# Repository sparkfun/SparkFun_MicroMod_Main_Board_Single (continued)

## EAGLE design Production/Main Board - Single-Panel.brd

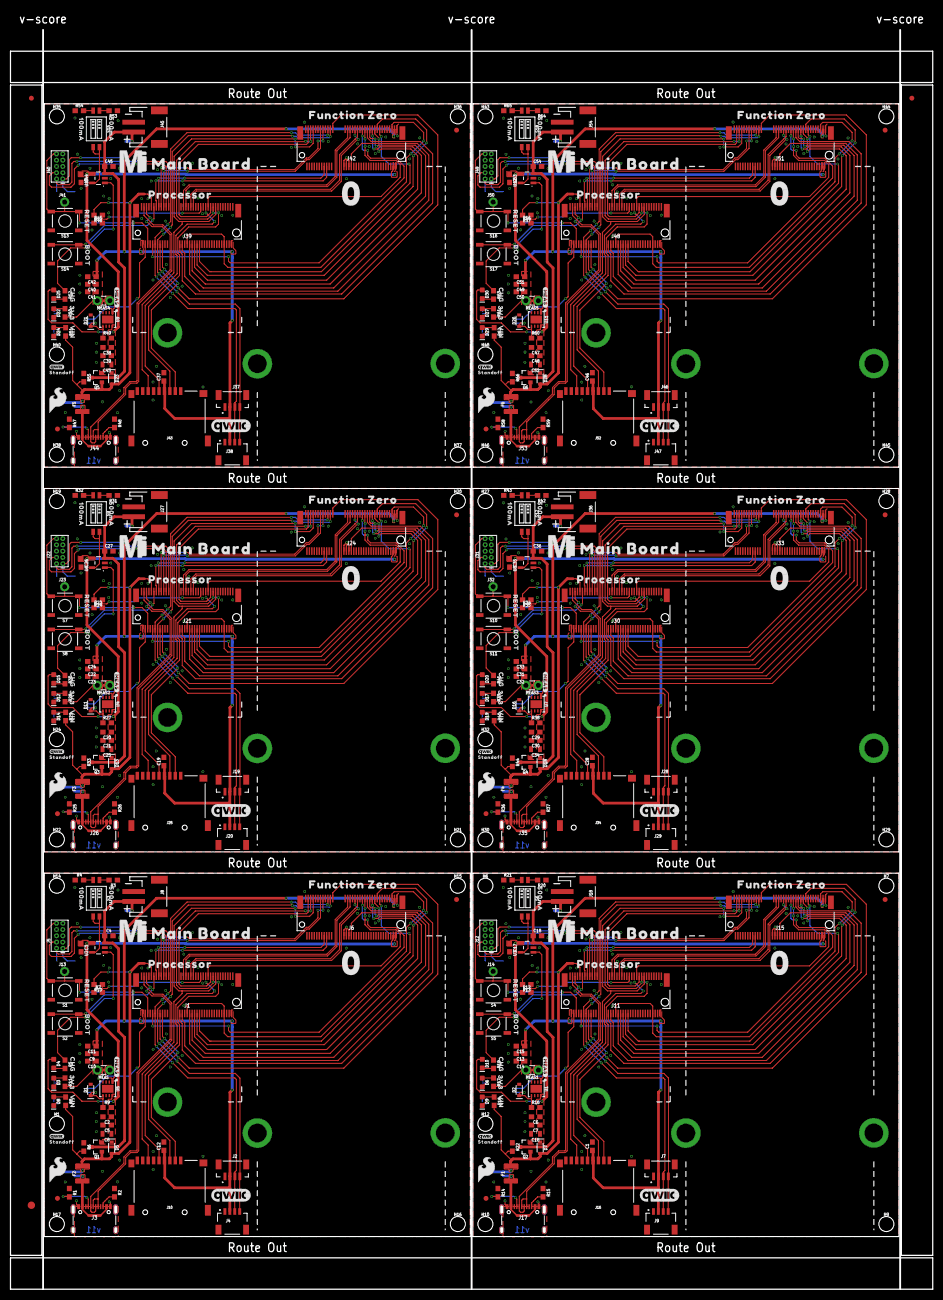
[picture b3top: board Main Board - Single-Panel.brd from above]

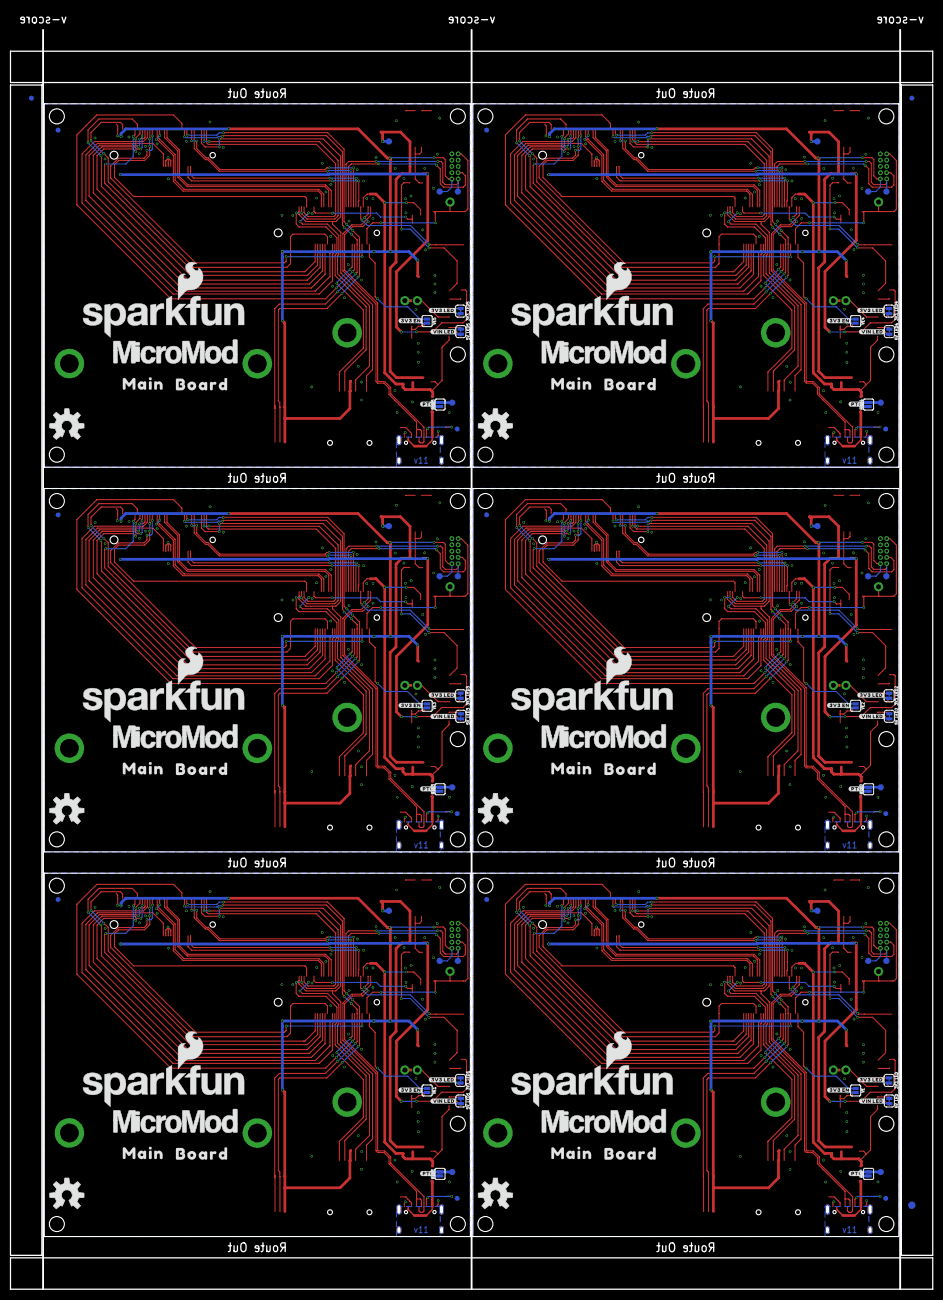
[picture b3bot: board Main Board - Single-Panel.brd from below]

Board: 2 copper layers, 186.9 x 255.3 mm, 534 parts (117 on the bottom side), 312 nets.

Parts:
3V3_LED, 3V3_LED1, 3V3_LED2, 3V3_LED3, 3V3_LED4, 3V3_LED5, 5V_LED, 5V_LED1, 5V_LED2, 5V_LED3, 5V_LED4, 5V_LED5: SMT-JUMPER_2_NC_TRACE_SILK
BYP, BYP1, BYP2, BYP3, BYP4, BYP5: JUMPER-SMT_2_NO_SILK; SMT-JUMPER_2_NO_SILK
C1, C5, C7, C10, C12, C14, C19, C21, C23, C28, C30, C32, C37, C39, C41, C46, C48, C50: 0.1uF; 0603
C2, C6, C11, C15, C20, C24, C29, C33, C38, C42, C47, C51: 0.22uF; 0603
C3, C4, C17, C18, C26, C27, C35, C36, C44, C45, C53, C54: 4.7uF; 0603
C8, C16, C25, C34, C43, C52: 10uF; 0805
C9, C13, C22, C31, C40, C49: 1.0uF; 0603
D1, D2, D11, D16, D21, D26: 3.3V; SOD-323
D3, D6, D8, D9, D12, D14, D17, D19, D22, D24, D27, D29: RED; LED-0603
D4, D10, D15, D20, D25, D30: Yellow; LED-0603
D5, D7, D13, D18, D23, D28: 3A/10V/280mV; SOD-323
E$1, E$2, E$3, E$4: FIDUCIAL-1X2
E$5, E$6: FIDUCIAL-1.5X3
F1, F2, F3, F4, F5, F6: 6V/2A; 1210
FD1, FD2, FD3, FD4, FD5, FD6, FD7, FD8, FD9, FD10, FD11, FD12, FD13, FD14, FD15, FD16, FD17, FD18, FD19, FD20, FD21, FD22, FD23, FD24: FIDUCIAL1X2; FIDUCIAL-1X2
H1, H6, H7, H9, H10, H12, H14, H15, H16, H17, H19, H20, H21, H22, H24, H27, H28, H29, H30, H32, H35, H36, H37, H38, H40, H43, H44, H45, H46, H48: STAND-OFFTIGHT; STAND-OFF-TIGHT
H2, H3, H4, H5, H8, H11, H13, H18, H23, H25, H26, H31, H33, H34, H39, H41, H42, H47: STAND-OFF-REFLOW-M2.5_2.5MM_TALL; STAND-OFF-REFLOW-M2.5
J1, J11, J21, J30, J39, J48: MICROMOD-2222-C; M.2-CONNECTOR-E
J2, J7, J19, J28, J37, J46: Vertical Qwiic Connector; JST04_1MM_VERT
J3, J17, J26, J35, J44, J53: USB-C-16P-2LAYER-PADS
J4, J9, J20, J29, J38, J47: QWIIC_RIGHT_ANGLE; JST04_1MM_RA
J5, J12, J22, J31, J40, J49: CORTEX_JTAG_DEBUG_MINIMUM_PTH; 2X5-PTH-1.27MM
J6, J15, J24, J33, J42, J51: MICROMOD_CARRIER; M.2-CONNECTOR-E-FUNCTION-STANDARD
J8, J18, J27, J36, J45, J54: JST-2-SMD
J10, J16, J25, J34, J43, J52: MICRO-SD-PUSH-PUSH-EXT-PIN; MICROSD-EXTERNALPIN
J13, J14, J23, J32, J41, J50: 1X01_NO_SILK
LOGO1, LOGO4, LOGO7, LOGO10, LOGO13, LOGO16: QWIIC_LOGO_8MM; QWIIC_8MM
LOGO2, LOGO5, LOGO8, LOGO11, LOGO14, LOGO17: SFE_LOGO_NAME_FLAME.3_INCH; SFE_LOGO_NAME_FLAME_.3
LOGO3, LOGO6, LOGO9, LOGO12, LOGO15, LOGO18: OSHW-LOGOL; OSHW-LOGO-L
MEAS, MEAS1, MEAS2, MEAS3, MEAS4, MEAS5: JUMPER-COMBO_2_NC_TRACE; COMBO-JUMPER_2_NC_TRACE
Q1, Q2, Q3, Q4, Q5, Q6: 3.1A/30V/105mΩ; SOT23-3
R1, R2, R14, R15, R25, R26, R36, R37, R47, R48, R58, R59: 5.1k; 0603
R3, R20, R31, R42, R53, R64: 2.0k; 0603
R4, R6, R7, R12, R21, R22, R23, R32, R33, R34, R43, R44, R45, R54, R55, R56, R65, R66: 10k; 0603
R5, R11, R17, R19, R28, R30, R39, R41, R50, R52, R61, R63: 1k; 0603
R8, R18, R29, R40, R51, R62: 4.7k; 0603
R9, R16, R27, R38, R49, R60: 100k; 0603
R10, R13, R24, R35, R46, R57: 20k; 0603
S1, S4, S7, S10, S13, S16: Reset; TACTILE_SWITCH_SMD_5.2MM
S2, S5, S8, S11, S14, S17: BOOT; TACTILE_SWITCH_SMD_5.2MM
S3, S6, S9, S12, S15, S18: DIP-02-SMD-50MIL; DIPSWITCH-02-50MIL
TP1, TP2, TP3, TP4, TP5, TP6, TP7, TP8, TP9, TP10, TP11, TP12, TP13, TP14, TP15, TP16, TP17, TP18, TP19, TP20, TP21, TP22, TP23, TP24: TEST-POINT3X5; PAD.03X.05
U1, U4, U5, U7, U9, U11: AP7361C-33; UDFN-8
U2, U3, U6, U8, U10, U12: MCP73831; SOT23-5
U$1, U$24, U$47, U$70, U$93, U$116: 3V332530
U$2, U$25, U$48, U$71, U$94, U$117: VIN32529
U$3, U$26, U$49, U$72, U$95, U$118: CHG32528
U$4, U$27, U$50, U$73, U$96, U$119: FUNCTION_ZERO517
U$5, U$28, U$51, U$74, U$97, U$120: PROCESSOR522
U$6, U$29, U$52, U$75, U$98, U$121: #3V3_LED#17
U$7, U$30, U$53, U$76, U$99, U$122: #VIN_LED#16
U$8, U$31, U$54, U$77, U$100, U$123: #PTC#18
U$9, U$32, U$55, U$78, U$101, U$124: BOOT32541
U$10, U$33, U$56, U$79, U$102, U$125: RESET32540
U$11, U$34, U$57, U$80, U$103, U$126: #3V3_EN#18
U$12, U$35, U$58, U$81, U$104, U$127: MICROMOD_MI_LOGO_1
U$13, U$36, U$59, U$82, U$105, U$128: 0525
U$14, U$42, U$65, U$88, U$111, U$134: MICROMOD_LOGO_1
U$15, U$37, U$60, U$83, U$106, U$129: MAIN523
U$16, U$38, U$61, U$84, U$107, U$130: BOARD524
U$17, U$39, U$62, U$85, U$108, U$131: 100MA6
U$18, U$40, U$63, U$86, U$109, U$132: 500MA101
U$19, U$41, U$64, U$87, U$110, U$133: MAIN_BOARD5523
U$20, U$43, U$66, U$89, U$112, U$135: QWIIC_3MM
U$21, U$44, U$67, U$90, U$113, U$136: STANDOFF501
U$22, U$45, U$68, U$91, U$114, U$137: SFE_LOGO_FLAME_.2
U$23, U$46, U$69, U$92, U$115, U$138: #MEAS#40313513
VE, VE1, VE2, VE3, VE4, VE5: SMT-JUMPER_2_NO_SILK

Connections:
3.3V: C9.1, C10.1, C11.1, C12.1, J1.2, J1.74, J2.2, J4.2, J5.1, J6.73, J10.4, MEAS.2, MEAS.4, R11.2, TP2.1
3.3V1: C1.1, C13.1, C14.1, C15.1, J7.2, J9.2, J11.2, J11.74, J12.1, J15.73, J16.4, MEAS1.2, MEAS1.4, R17.2, TP5.1
3.3V2: C19.1, C22.1, C23.1, C24.1, J19.2, J20.2, J21.2, J21.74, J22.1, J24.73, J25.4, MEAS2.2, MEAS2.4, R28.2, TP9.1
3.3V3: C28.1, C31.1, C32.1, C33.1, J28.2, J29.2, J30.2, J30.74, J31.1, J33.73, J34.4, MEAS3.2, MEAS3.4, R39.2, TP13.1
3.3V4: C37.1, C40.1, C41.1, C42.1, J37.2, J38.2, J39.2, J39.74, J40.1, J42.73, J43.4, MEAS4.2, MEAS4.4, R50.2, TP17.1
3.3V5: C46.1, C49.1, C50.1, C51.1, J46.2, J47.2, J48.2, J48.74, J49.1, J51.73, J52.4, MEAS5.2, MEAS5.4, R61.2, TP21.1
3.3V_EN: J1.4, VE.1
3.3V_EN1: J11.4, VE1.1
3.3V_EN2: J21.4, VE2.1
3.3V_EN3: J30.4, VE3.1
3.3V_EN4: J39.4, VE4.1
3.3V_EN5: J48.4, VE5.1
3.3V_EN_VE: D1.C, R9.1, U5.5, VE.2
3.3V_EN_VE1: D2.C, R16.1, U1.5, VE1.2
3.3V_EN_VE2: D11.C, R27.1, U4.5, VE2.2
3.3V_EN_VE3: D16.C, R38.1, U7.5, VE3.2
3.3V_EN_VE4: D21.C, R49.1, U9.5, VE4.2
3.3V_EN_VE5: D26.C, R60.1, U11.5, VE5.2
!BOOT!: J1.11, S2.3, S2.4
!BOOT!1: J11.11, S5.3, S5.4
!BOOT!2: J21.11, S8.3, S8.4
!BOOT!3: J30.11, S11.3, S11.4
!BOOT!4: J39.11, S14.3, S14.4
!BOOT!5: J48.11, S17.3, S17.4
!CS0!-PROCESSOR: J1.55, J6.49
!CS0!-PROCESSOR1: J11.55, J15.49
!CS0!-PROCESSOR2: J21.55, J24.49
!CS0!-PROCESSOR3: J30.55, J33.49
!CS0!-PROCESSOR4: J39.55, J42.49
!CS0!-PROCESSOR5: J48.55, J51.49
!RESET!: J1.6, J5.10, J13.1, S1.3, S1.4
!RESET!1: J11.6, J12.10, J14.1, S4.3, S4.4
!RESET!2: J21.6, J22.10, J23.1, S7.3, S7.4
!RESET!3: J30.6, J31.10, J32.1, S10.3, S10.4
!RESET!4: J39.6, J40.10, J41.1, S13.3, S13.4
!RESET!5: J48.6, J49.10, J50.1, S16.3, S16.4
A0-PROCESSOR: J1.34, J6.38
A0-PROCESSOR1: J11.34, J15.38
A0-PROCESSOR2: J21.34, J24.38
A0-PROCESSOR3: J30.34, J33.38
A0-PROCESSOR4: J39.34, J42.38
A0-PROCESSOR5: J48.34, J51.38
CTS1-PROCESSOR: J1.15, J6.16
CTS1-PROCESSOR1: J11.15, J15.16
CTS1-PROCESSOR2: J21.15, J24.16
CTS1-PROCESSOR3: J30.15, J33.16
CTS1-PROCESSOR4: J39.15, J42.16
CTS1-PROCESSOR5: J48.15, J51.16
D0-PROCESSOR: J1.10, J6.47
D0-PROCESSOR1: J11.10, J15.47
D0-PROCESSOR2: J21.10, J24.47
D0-PROCESSOR3: J30.10, J33.47
D0-PROCESSOR4: J39.10, J42.47
D0-PROCESSOR5: J48.10, J51.47
D1-PROCESSOR/SD_CARD_!CS!: J1.18, J10.2
D1-PROCESSOR/SD_CARD_!CS!1: J11.18, J16.2
D1-PROCESSOR/SD_CARD_!CS!2: J21.18, J25.2
D1-PROCESSOR/SD_CARD_!CS!3: J30.18, J34.2
D1-PROCESSOR/SD_CARD_!CS!4: J39.18, J43.2
D1-PROCESSOR/SD_CARD_!CS!5: J48.18, J52.2
D+: J1.3, J3.A6, J3.B6
D+1: J11.3, J17.A6, J17.B6
D+2: J21.3, J26.A6, J26.B6
D+3: J30.3, J35.A6, J35.B6
D+4: J39.3, J44.A6, J44.B6
D+5: J48.3, J53.A6, J53.B6
D-: J1.5, J3.A7, J3.B7
D-1: J11.5, J17.A7, J17.B7
D-2: J21.5, J26.A7, J26.B7
D-3: J30.5, J35.A7, J35.B7
D-4: J39.5, J44.A7, J44.B7
D-5: J48.5, J53.A7, J53.B7
G0-PROCESSOR: J1.40, J6.53
G0-PROCESSOR1: J11.40, J15.53
G0-PROCESSOR2: J21.40, J24.53
G0-PROCESSOR3: J30.40, J33.53
G0-PROCESSOR4: J39.40, J42.53
G0-PROCESSOR5: J48.40, J51.53
G1-PROCESSOR: J1.42, J6.55
G1-PROCESSOR1: J11.42, J15.55
G1-PROCESSOR2: J21.42, J24.55
G1-PROCESSOR3: J30.42, J33.55
G1-PROCESSOR4: J39.42, J42.55
G1-PROCESSOR5: J48.42, J51.55
G2-PROCESSOR: J1.44, J6.57
G2-PROCESSOR1: J11.44, J15.57
G2-PROCESSOR2: J21.44, J24.57
G2-PROCESSOR3: J30.44, J33.57
G2-PROCESSOR4: J39.44, J42.57
G2-PROCESSOR5: J48.44, J51.57
G3-PROCESSOR: J1.46, J6.59
G3-PROCESSOR1: J11.46, J15.59
G3-PROCESSOR2: J21.46, J24.59
G3-PROCESSOR3: J30.46, J33.59
G3-PROCESSOR4: J39.46, J42.59
G3-PROCESSOR5: J48.46, J51.59
G4-PROCESSOR: J1.48, J6.61
G4-PROCESSOR1: J11.48, J15.61
G4-PROCESSOR2: J21.48, J24.61
G4-PROCESSOR3: J30.48, J33.61
G4-PROCESSOR4: J39.48, J42.61
G4-PROCESSOR5: J48.48, J51.61
GND: 3V3_LED.1, 5V_LED.1, C2.2, C3.2, C4.2, C5.2, C8.2, C9.2, C10.2, C11.2, C12.2, D1.A, H3.1, H4.1, H8.1, J1.1, J1.7, J1.33, J1.36, J1.39, J1.45, J1.75, J2.1, J3.GND, J3.GND2, J4.1, J5.3, J5.5, J5.9, J6.1, J6.32, J6.33, J6.34, J6.36, J6.39, J6.45, J6.75, J8.1, J10.6, J10.10, J10.11, J10.12, J10.13, R1.1, R2.1, R3.1, R4.1, R6.1, R7.1, S1.1, S1.2, S2.1, S2.2, U2.2, U5.4, U5.EP
GND1: 3V3_LED1.1, 5V_LED1.1, C1.2, C6.2, C7.2, C13.2, C14.2, C15.2, C16.2, C17.2, C18.2, D2.A, H2.1, H5.1, H11.1, J7.1, J9.1, J11.1, J11.7, J11.33, J11.36, J11.39, J11.45, J11.75, J12.3, J12.5, J12.9, J15.1, J15.32, J15.33, J15.34, J15.36, J15.39, J15.45, J15.75, J16.6, J16.10, J16.11, J16.12, J16.13, J17.GND, J17.GND2, J18.1, R12.1, R14.1, R15.1, R20.1, R21.1, R22.1, S4.1, S4.2, S5.1, S5.2, U1.4, U1.EP, U3.2
GND2: 3V3_LED2.1, 5V_LED2.1, C19.2, C20.2, C21.2, C22.2, C23.2, C24.2, C25.2, C26.2, C27.2, D11.A, H13.1, H18.1, H23.1, J19.1, J20.1, J21.1, J21.7, J21.33, J21.36, J21.39, J21.45, J21.75, J22.3, J22.5, J22.9, J24.1, J24.32, J24.33, J24.34, J24.36, J24.39, J24.45, J24.75, J25.6, J25.10, J25.11, J25.12, J25.13, J26.GND, J26.GND2, J27.1, R23.1, R25.1, R26.1, R31.1, R32.1, R33.1, S7.1, S7.2, S8.1, S8.2, U4.4, U4.EP, U6.2
GND3: 3V3_LED3.1, 5V_LED3.1, C28.2, C29.2, C30.2, C31.2, C32.2, C33.2, C34.2, C35.2, C36.2, D16.A, H25.1, H26.1, H31.1, J28.1, J29.1, J30.1, J30.7, J30.33, J30.36, J30.39, J30.45, J30.75, J31.3, J31.5, J31.9, J33.1, J33.32, J33.33, J33.34, J33.36, J33.39, J33.45, J33.75, J34.6, J34.10, J34.11, J34.12, J34.13, J35.GND, J35.GND2, J36.1, R34.1, R36.1, R37.1, R42.1, R43.1, R44.1, S10.1, S10.2, S11.1, S11.2, U7.4, U7.EP, U8.2
GND4: 3V3_LED4.1, 5V_LED4.1, C37.2, C38.2, C39.2, C40.2, C41.2, C42.2, C43.2, C44.2, C45.2, D21.A, H33.1, H34.1, H39.1, J37.1, J38.1, J39.1, J39.7, J39.33, J39.36, J39.39, J39.45, J39.75, J40.3, J40.5, J40.9, J42.1, J42.32, J42.33, J42.34, J42.36, J42.39, J42.45, J42.75, J43.6, J43.10, J43.11, J43.12, J43.13, J44.GND, J44.GND2, J45.1, R45.1, R47.1, R48.1, R53.1, R54.1, R55.1, S13.1, S13.2, S14.1, S14.2, U9.4, U9.EP, U10.2
GND5: 3V3_LED5.1, 5V_LED5.1, C46.2, C47.2, C48.2, C49.2, C50.2, C51.2, C52.2, C53.2, C54.2, D26.A, H41.1, H42.1, H47.1, J46.1, J47.1, J48.1, J48.7, J48.33, J48.36, J48.39, J48.45, J48.75, J49.3, J49.5, J49.9, J51.1, J51.32, J51.33, J51.34, J51.36, J51.39, J51.45, J51.75, J52.6, J52.10, J52.11, J52.12, J52.13, J53.GND, J53.GND2, J54.1, R56.1, R58.1, R59.1, R64.1, R65.1, R66.1, S16.1, S16.2, S17.1, S17.2, U11.4, U11.EP, U12.2
HOST_D+: J1.35, J6.35
HOST_D+1: J11.35, J15.35
HOST_D+2: J21.35, J24.35
HOST_D+3: J30.35, J33.35
HOST_D+4: J39.35, J42.35
HOST_D+5: J48.35, J51.35
HOST_D-: J1.37, J6.37
HOST_D-1: J11.37, J15.37
HOST_D-2: J21.37, J24.37
HOST_D-3: J30.37, J33.37
HOST_D-4: J39.37, J42.37
HOST_D-5: J48.37, J51.37
I2C_!INT!: J1.16, J6.23
I2C_!INT!1: J11.16, J15.23
I2C_!INT!2: J21.16, J24.23
I2C_!INT!3: J30.16, J33.23
I2C_!INT!4: J39.16, J42.23
I2C_!INT!5: J48.16, J51.23
I2C_SCL: J1.14, J2.4, J4.4, J6.21
I2C_SCL1: J7.4, J9.4, J11.14, J15.21
I2C_SCL2: J19.4, J20.4, J21.14, J24.21
I2C_SCL3: J28.4, J29.4, J30.14, J33.21
I2C_SCL4: J37.4, J38.4, J39.14, J42.21
I2C_SCL5: J46.4, J47.4, J48.14, J51.21
I2C_SDA: J1.12, J2.3, J4.3, J6.19
I2C_SDA1: J7.3, J9.3, J11.12, J15.19
I2C_SDA2: J19.3, J20.3, J21.12, J24.19
I2C_SDA3: J28.3, J29.3, J30.12, J33.19
I2C_SDA4: J37.3, J38.3, J39.12, J42.19
I2C_SDA5: J46.3, J47.3, J48.12, J51.19
unnamed: J17.B5, R15.2
unnamed: MEAS.1, MEAS.3, U5.1
unnamed: D3.A, R11.1
unnamed: J3.B5, R2.2
unnamed: J3.A5, R1.2
unnamed: BYP.1, F2.1, J3.VBUS1, J3.VBUS2
unnamed: R3.2, S3.1
unnamed: S3.3, S3.4, U2.5
unnamed: 5V_LED.2, D8.C
unnamed: 3V3_LED.2, D3.C
unnamed: R4.2, S3.2
unnamed: D8.A, R8.1
unnamed: J17.A5, R14.2
unnamed: D4.C, R5.2
unnamed: R5.1, U2.1
unnamed: MEAS1.1, MEAS1.3, U1.1
unnamed: D6.A, R17.1
unnamed: BYP1.1, F1.1, J17.VBUS1, J17.VBUS2
unnamed: D9.A, R18.1
unnamed: 5V_LED1.2, D9.C
unnamed: 3V3_LED1.2, D6.C
unnamed: S6.3, S6.4, U3.5
unnamed: D10.C, R19.2
unnamed: R19.1, U3.1
unnamed: R20.2, S6.1
unnamed: R21.2, S6.2
unnamed: J26.B5, R26.2
unnamed: J26.A5, R25.2
unnamed: MEAS2.1, MEAS2.3, U4.1
unnamed: D12.A, R28.1
unnamed: BYP2.1, F3.1, J26.VBUS1, J26.VBUS2
unnamed: D14.A, R29.1
unnamed: 5V_LED2.2, D14.C
unnamed: 3V3_LED2.2, D12.C
unnamed: S9.3, S9.4, U6.5
unnamed: D15.C, R30.2
unnamed: R30.1, U6.1
unnamed: R31.2, S9.1
unnamed: R32.2, S9.2
unnamed: J35.B5, R37.2
unnamed: J35.A5, R36.2
unnamed: MEAS3.1, MEAS3.3, U7.1
unnamed: D17.A, R39.1
unnamed: BYP3.1, F4.1, J35.VBUS1, J35.VBUS2
unnamed: D19.A, R40.1
unnamed: 5V_LED3.2, D19.C
unnamed: 3V3_LED3.2, D17.C
unnamed: S12.3, S12.4, U8.5
unnamed: D20.C, R41.2
unnamed: R41.1, U8.1
unnamed: R42.2, S12.1
unnamed: R43.2, S12.2
unnamed: J44.B5, R48.2
unnamed: J44.A5, R47.2
unnamed: MEAS4.1, MEAS4.3, U9.1
unnamed: D22.A, R50.1
unnamed: BYP4.1, F5.1, J44.VBUS1, J44.VBUS2
unnamed: D24.A, R51.1
unnamed: 5V_LED4.2, D24.C
unnamed: 3V3_LED4.2, D22.C
unnamed: S15.3, S15.4, U10.5
unnamed: D25.C, R52.2
unnamed: R52.1, U10.1
unnamed: R53.2, S15.1
unnamed: R54.2, S15.2
unnamed: J53.B5, R59.2
unnamed: J53.A5, R58.2
unnamed: MEAS5.1, MEAS5.3, U11.1
unnamed: D27.A, R61.1
unnamed: BYP5.1, F6.1, J53.VBUS1, J53.VBUS2
unnamed: D29.A, R62.1
unnamed: 5V_LED5.2, D29.C
unnamed: 3V3_LED5.2, D27.C
unnamed: S18.3, S18.4, U12.5
unnamed: D30.C, R63.2
unnamed: R63.1, U12.1
unnamed: R64.2, S18.1
unnamed: R65.2, S18.2
PROCESSOR_CAN-RX: J1.41, J6.43
PROCESSOR_CAN-RX1: J11.41, J15.43
PROCESSOR_CAN-RX2: J21.41, J24.43
PROCESSOR_CAN-RX3: J30.41, J33.43
PROCESSOR_CAN-RX4: J39.41, J42.43
PROCESSOR_CAN-RX5: J48.41, J51.43
PROCESSOR_CAN-TX: J1.43, J6.41
PROCESSOR_CAN-TX1: J11.43, J15.41
PROCESSOR_CAN-TX2: J21.43, J24.41
PROCESSOR_CAN-TX3: J30.43, J33.41
PROCESSOR_CAN-TX4: J39.43, J42.41
PROCESSOR_CAN-TX5: J48.43, J51.41
PWM0-PROCESSOR: J1.32, J6.51
PWM0-PROCESSOR1: J11.32, J15.51
PWM0-PROCESSOR2: J21.32, J24.51
PWM0-PROCESSOR3: J30.32, J33.51
PWM0-PROCESSOR4: J39.32, J42.51
PWM0-PROCESSOR5: J48.32, J51.51
PWR_EN0: J1.38, J1.68, J6.71
PWR_EN1: J11.38, J11.68, J15.71
PWR_EN2: J21.38, J21.68, J24.71
PWR_EN3: J30.38, J30.68, J33.71
PWR_EN4: J39.38, J39.68, J42.71
PWR_EN5: J48.38, J48.68, J51.71
RTS1-PROCESSOR: J1.13, J6.18
RTS1-PROCESSOR1: J11.13, J15.18
RTS1-PROCESSOR2: J21.13, J24.18
RTS1-PROCESSOR3: J30.13, J33.18
RTS1-PROCESSOR4: J39.13, J42.18
RTS1-PROCESSOR5: J48.13, J51.18
RX1-PROCESSOR: J1.19, J6.13
RX1-PROCESSOR1: J11.19, J15.13
RX1-PROCESSOR2: J21.19, J24.13
RX1-PROCESSOR3: J30.19, J33.13
RX1-PROCESSOR4: J39.19, J42.13
RX1-PROCESSOR5: J48.19, J51.13
SPI_PROCESSOR_SCK: J1.57, J6.3, J10.5
SPI_PROCESSOR_SCK1: J11.57, J15.3, J16.5
SPI_PROCESSOR_SCK2: J21.57, J24.3, J25.5
SPI_PROCESSOR_SCK3: J30.57, J33.3, J34.5
SPI_PROCESSOR_SCK4: J39.57, J42.3, J43.5
SPI_PROCESSOR_SCK5: J48.57, J51.3, J52.5
SPI_PROCESSOR_SDI: J1.61, J6.7, J10.7
SPI_PROCESSOR_SDI1: J11.61, J15.7, J16.7
SPI_PROCESSOR_SDI2: J21.61, J24.7, J25.7
SPI_PROCESSOR_SDI3: J30.61, J33.7, J34.7
SPI_PROCESSOR_SDI4: J39.61, J42.7, J43.7
SPI_PROCESSOR_SDI5: J48.61, J51.7, J52.7
SPI_PROCESSOR_SDO: J1.59, J6.5, J10.3
SPI_PROCESSOR_SDO1: J11.59, J15.5, J16.3
SPI_PROCESSOR_SDO2: J21.59, J24.5, J25.3
SPI_PROCESSOR_SDO3: J30.59, J33.5, J34.3
SPI_PROCESSOR_SDO4: J39.59, J42.5, J43.3
SPI_PROCESSOR_SDO5: J48.59, J51.5, J52.3
SWDCK: J1.21, J5.4
SWDCK1: J11.21, J12.4
SWDCK2: J21.21, J22.4
SWDCK3: J30.21, J31.4
SWDCK4: J39.21, J40.4
SWDCK5: J48.21, J49.4
SWDIO: J1.23, J5.2, TP1.1
SWDIO1: J11.23, J12.2, TP8.1
SWDIO2: J21.23, J22.2, TP12.1
SWDIO3: J30.23, J31.2, TP16.1
SWDIO4: J39.23, J40.2, TP20.1
SWDIO5: J48.23, J49.2, TP24.1
TX1-PROCESSOR: J1.17, J6.15
TX1-PROCESSOR1: J11.17, J15.15
TX1-PROCESSOR2: J21.17, J24.15
TX1-PROCESSOR3: J30.17, J33.15
TX1-PROCESSOR4: J39.17, J42.15
TX1-PROCESSOR5: J48.17, J51.15
VCC: C2.1, C3.1, C5.1, C8.1, D4.A, D5.C, J6.72, J6.74, Q1.2, R9.2, U2.4, U5.8
VCC1: C6.1, C7.1, C16.1, C17.1, D7.C, D10.A, J15.72, J15.74, Q2.2, R16.2, U1.8, U3.4
VCC2: C20.1, C21.1, C25.1, C26.1, D13.C, D15.A, J24.72, J24.74, Q3.2, R27.2, U4.8, U6.4
VCC3: C29.1, C30.1, C34.1, C35.1, D18.C, D20.A, J33.72, J33.74, Q4.2, R38.2, U7.8, U8.4
VCC4: C38.1, C39.1, C43.1, C44.1, D23.C, D25.A, J42.72, J42.74, Q5.2, R49.2, U9.8, U10.4
VCC5: C47.1, C48.1, C52.1, C53.1, D28.C, D30.A, J51.72, J51.74, Q6.2, R60.2, U11.8, U12.4
VIN: BYP.2, D5.A, F2.2, J1.9, Q1.1, R6.2, R8.2, R10.2, TP4.1
VIN1: BYP1.2, D7.A, F1.2, J11.9, Q2.1, R13.2, R18.2, R22.2, TP7.1
VIN2: BYP2.2, D13.A, F3.2, J21.9, Q3.1, R24.2, R29.2, R33.2, TP11.1
VIN3: BYP3.2, D18.A, F4.2, J30.9, Q4.1, R35.2, R40.2, R44.2, TP15.1
VIN4: BYP4.2, D23.A, F5.2, J39.9, Q5.1, R46.2, R51.2, R55.2, TP19.1
VIN5: BYP5.2, D28.A, F6.2, J48.9, Q6.1, R57.2, R62.2, R66.2, TP23.1
VIN/1: J11.49, R12.2, R13.1
VIN/2: J21.49, R23.2, R24.1
VIN/3: J1.49, R7.2, R10.1
VIN/4: J30.49, R34.2, R35.1
VIN/5: J39.49, R45.2, R46.1
VIN/6: J48.49, R56.2, R57.1
V_BATT: C4.1, J8.2, Q1.3, TP3.1, U2.3
V_BATT1: C18.1, J18.2, Q2.3, TP6.1, U3.3
V_BATT2: C27.1, J27.2, Q3.3, TP10.1, U6.3
V_BATT3: C36.1, J36.2, Q4.3, TP14.1, U8.3
V_BATT4: C45.1, J45.2, Q5.3, TP18.1, U10.3
V_BATT5: C54.1, J54.2, Q6.3, TP22.1, U12.3

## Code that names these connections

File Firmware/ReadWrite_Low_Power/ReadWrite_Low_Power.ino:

/*
  SD Card Read/Write

  This example shows how to read and write data to and from an SD card file
  The circuit:

  SD card attached to SPI bus as follows:

   SD Card   <=> MicroMod Main Board <=> Artemis Processor Board
   -----------------------------------------------------------------
   SD ENABLE <=>  I2C_SDA1-PROCESSOR <=> pin 9
   PICO/SDO  <=>  SPI_PROCESSOR_SDO  <=> pin 38
   POCI/SDI  <=>  SPI_PROCESSOR_SDI  <=> pin 43
   CLK       <=>  SPI_PROCESSOR_SCK  <=> pin 42
   CS        <=>  D1_PROCESSOR       <=> pin 1 (Main Board - Single)
   or ...
   CS        <=>  G4_PROCESSOR       <=> pin 28 (Main Board - Double)

  created   Nov 2010
  by David A. Mellis
  modified 9 Apr 2012
  by Tom Igoe

  This example code is in the public domain.

*/

#include <SPI.h>
#include <SD.h>

//==========ARTEMIS==========
// The microSD Card CS pin is D1 for the MicroMod Main Board - Single and Artemis Processor (D1). Adjust for your processor if necessary.
const int SD_CS_PIN = 1;
// The microSD Card's CS pin is G4 for the MicroMod Main Board - Double and Artemis Processor (D28). Adjust for your processor if necessary.
//const int SD_CS_PIN = 28; 

// The microSD Card CS pin is SDA1 for the MicroMod Main Board - Single and Artemis Processor (D9). Adjust for your processor if necessary.
const int SD_ENABLE = 9;

File myFile;

void setup() {

  pinMode(SD_ENABLE, OUTPUT);  //sets the digital pin as output
  digitalWrite(SD_ENABLE, LOW);  //Power MicroSD card socket, pin is active low

  // Open serial communications and wait for port to open:
  Serial.begin(9600);
  while (!Serial) {
    ; // wait for serial port to connect. Needed for native USB port only
  }


  Serial.print("Initializing SD card...");

  if (!SD.begin(SD_CS_PIN)) {
    Serial.println("initialization failed!");
    while (1);
  }
  Serial.println("initialization done.");

  // open the file. note that only one file can be open at a time,
  // so you have to close this one before opening another.
  myFile = SD.open("test.txt", FILE_WRITE);

  // if the file opened okay, write to it:
  if (myFile) {
    Serial.print("Writing to test.txt...");
    myFile.println("testing 1, 2, 3.");
    // close the file:
    myFile.close();
    Serial.println("done.");
  } else {
    // if the file didn't open, print an error:
    Serial.println("error opening test.txt");
  }

  // re-open the file for reading:
  myFile = SD.open("test.txt");
  if (myFile) {
    Serial.println("test.txt:");

    // read from the file until there's nothing else in it:
    while (myFile.available()) {
      Serial.write(myFile.read());
    }
    // close the file:
    myFile.close();
  } else {
    // if the file didn't open, print an error:
    Serial.println("error opening test.txt");
  }

  digitalWrite(SD_ENABLE, HIGH);  //remove power from MicroSD card socket for low power applications

}// end setup()

void loop() {
  // nothing happens after setup

}//end loop()

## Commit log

2021-08-17 Initial commit (post-prototype, pre finalized for REDs)
2021-08-17 Rename "Single Function Board" folder to "Hardware"
2021-08-31 Adds another standoff for qwiic boards around the lower left edge, adds silk
    * Removes jumper for "VIN/VUSB"
    * Correctly routes USB_VIN on processor connector to VIN
    * Double routes PWR_EN for ESP32 Processor boards
    * Moves SD Card up 0.04"
    * Adds more measures
2021-09-02 Adds 2 pin dip switch for charge selection, adds PCHAN MOSFET to VBATT net
    * Adds better silk
    * Moves stuff around schematic for better clarity
    * Adds charge table to schematic
2021-09-02 Replaces MOSFET with another one
2021-09-03 Adds 10k pulldown to gate on PCHAN MOSFET, fixes length measurement
2021-09-07 Adds prod_id to function board connector, double routes power enable to A1 and previous pin
2021-09-10 Moves SD Card slightly towards center of PCB
2021-09-10 Changes eagle file names
2021-09-10 Adds new panel
2021-09-10 Adds a larger manufacturing panel than the previous
2021-09-10 Adds new panel that is two columns of three
2021-10-11 Changes power to Function boards @ VCC to VCC and not VIN
2021-10-11 Rolls to V11
2021-10-22 Replaces shottky diode
2021-11-03 Updates function board symbol, fixes charging current value when 1 and 2 are flipped.
2021-11-08 remove MicroMod Main Board - Double reference
2021-11-10 Create ReadWrite.ino
    Included modified example with a microSD card from the SD Arduino Library
2021-11-11 Updates the design to use the Micromod-function device in the official SFE Eagle Libs
2022-07-21 Adds initial commit to Main Board Single v20
2022-07-21 Adds new board files?
2022-08-18 Adds completely updated design - update in Fusion360, imported back to Eagle 9 for silk
2022-08-18 Removes old versions
2022-08-18 Rolls version to v20
2022-08-19 * Adds 4-pin header for other DFU lines
    * Updates silk
    * Uses VIN as power supply to battery charger
    * Fixes PCH Mosfet
    * Fixes polygons where applicable
    * Adds SparkFun logo to topside.
2022-08-19 Adds qwiic LED silk
2022-08-19 Fixes airwire
2022-08-23 Renames board files
2022-08-23 Fixes measure pth alignment
2022-08-23 Adds new production files
2022-08-23 Remakes production files
2022-08-24 Updates silk on multiplexing PTH
2022-08-24 Updates production files
2022-08-24 Adds PROD_ID to UART switcher
2022-09-02 Updates PROD ID on VREG
2022-10-26 Routes PWM1 pin to power enable pin on function card
    * Rolls version to v21
    * Fixes PTC silk
2022-10-28 Rotates JST connector, fixes some silk labels
2022-10-28 Moves JST connector in 0.1"
2022-10-28 Adds notch for batteries, moves VBAT test point
2022-10-28 Renames files to match PCB version numver
2022-10-31 Fixes width DRC errors
2023-01-03 Updat input voltage range on the VREG
2023-01-04 Update ReadWrite.ino
    update code comments and notes
2023-01-04 Update MicroMod_Main_Board_Single_Enable_Function_Board.ino
    - update comments and notes
    - include updated GPIO pin to toggle PWR_EN0
2023-01-04 Create ReadWrite_Low_Power.ino
    Add example to toggle microSD card Socket's power for low power applications
2023-01-04 Create MicroMod_Main_Enable_Qwiic_Boards.ino
    Add example to toggle Qwiic Port's voltage regulator for low power
2023-05-03 Updates function board symbol
